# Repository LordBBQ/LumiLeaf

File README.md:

# LumiLeaf
Smart affordable adressable LED panels

### Assembly
##### Step 1

Remove the printed supports and adhesion materials from the part.

##### Step 2

Use a soldering iron to insert the 4 terminal heatset inserts.

Insert the M3 terminal bolts and washers into the inserts.

##### Step 3

Strip a length of solid core ethernet cable.

Separate the individual strands, and remove the twists as much as possible.

##### Step 4

Route the wires through the wire channel as shown.

##### Step 5

Cut a 250mm length of LED strip.

Adhere this around the edge of the light.

##### Step 6

Carefully solder the 4 wires to the 5V, GND, D+ and D- pins. This is very fiddly, and may require multiple attempts.

##### Step 7

Route the wires out the wire hole, and spread them to each of their terminals. 

Loop each wire around a bolt and tighten, ensuring there is no insulation clamped under the screw.

##### Step 8

Use a multimeter to check check for short circuts in the assembly.

##### Step 9

Cut out a triangular section of foil to act as the reflector.

Use a thin double sided tape to adhere the foil over the back panel.

>[!WARNING]
>Ensure the foil does not make contact with the LED strip or exposed wire. This could lead to a short circut!

##### Step 10
Repeat for all other desired modules. Attach the lasercut or 3D printed diffuser and bezel.

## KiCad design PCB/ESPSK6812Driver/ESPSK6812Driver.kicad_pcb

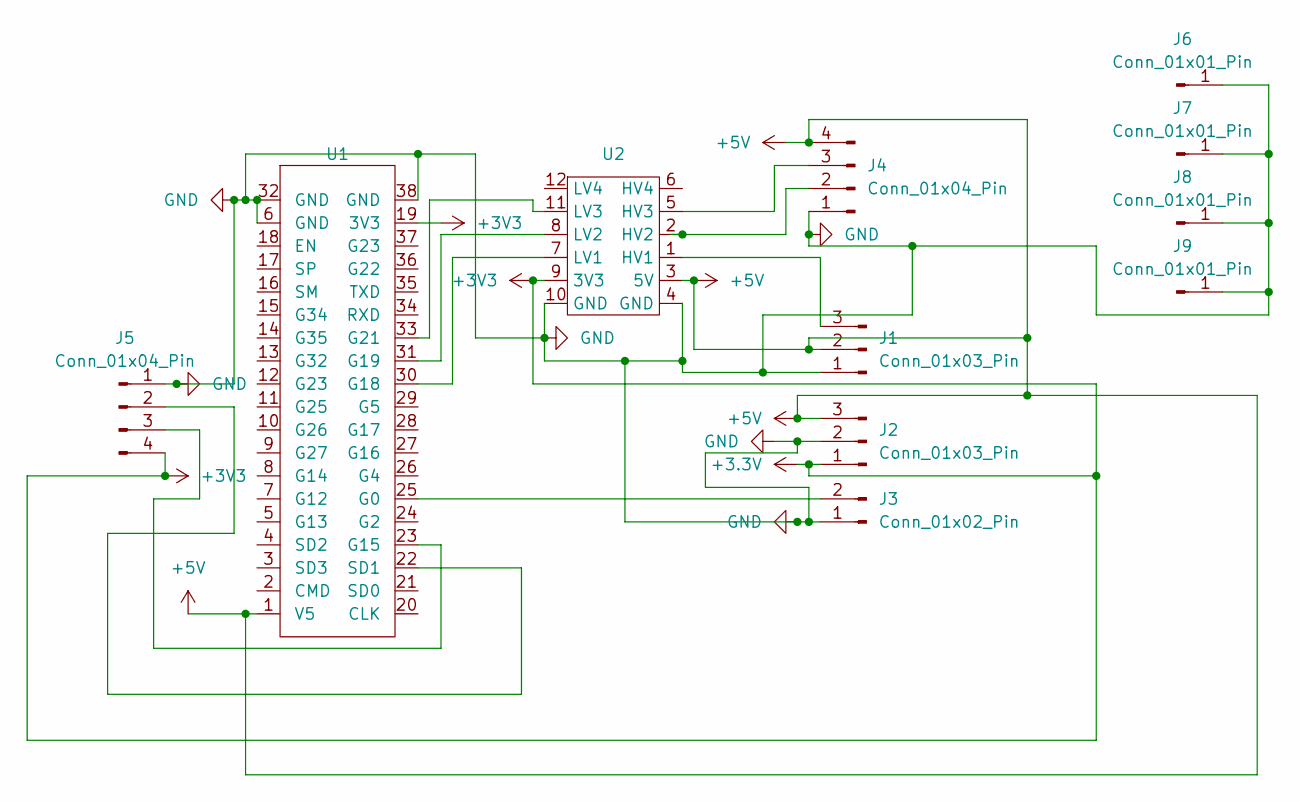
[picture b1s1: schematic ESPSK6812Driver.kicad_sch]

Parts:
J1, J2: Conn_01x03_Pin; JST_XH_B3B-XH-AM_1x03_P2.50mm_Vertical
J3: Conn_01x02_Pin; JST_XH_B2B-XH-AM_1x02_P2.50mm_Vertical
J4, J5: Conn_01x04_Pin; PinHeader_1x04_P2.54mm_Vertical
J6, J7, J8, J9: Conn_01x01_Pin; MountingHole_3.2mm_M3_DIN965_Pad
U1: ESPModuleJaycar
U2: LogicLevelShifterBidirectional

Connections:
+3.3V: J2.1, J5.4, U1.19 (3V3), U2.9 (3V3)
+5V: J1.2, J2.3, J4.4, U1.1 (V5), U2.3 (5V)
GND: J1.1, J2.2, J3.1, J4.1, J5.1, J6.1, J7.1, J8.1, J9.1, U1.6 (GND), U1.32 (GND), U1.38 (GND), U2.4 (GND), U2.10 (GND)
unnamed: J1.3, U2.1 (HV1)
unnamed: J3.2, U1.25 (G0)
unnamed: J4.2, U2.2 (HV2)
unnamed: J4.3, U2.5 (HV3)
unnamed: J5.2, U1.22 (SD1)
unnamed: J5.3, U1.23 (G15)
unnamed: U1.30 (G18), U2.7 (LV1)
unnamed: U1.31 (G19), U2.8 (LV2)
unnamed: U1.33 (G21), U2.11 (LV3)

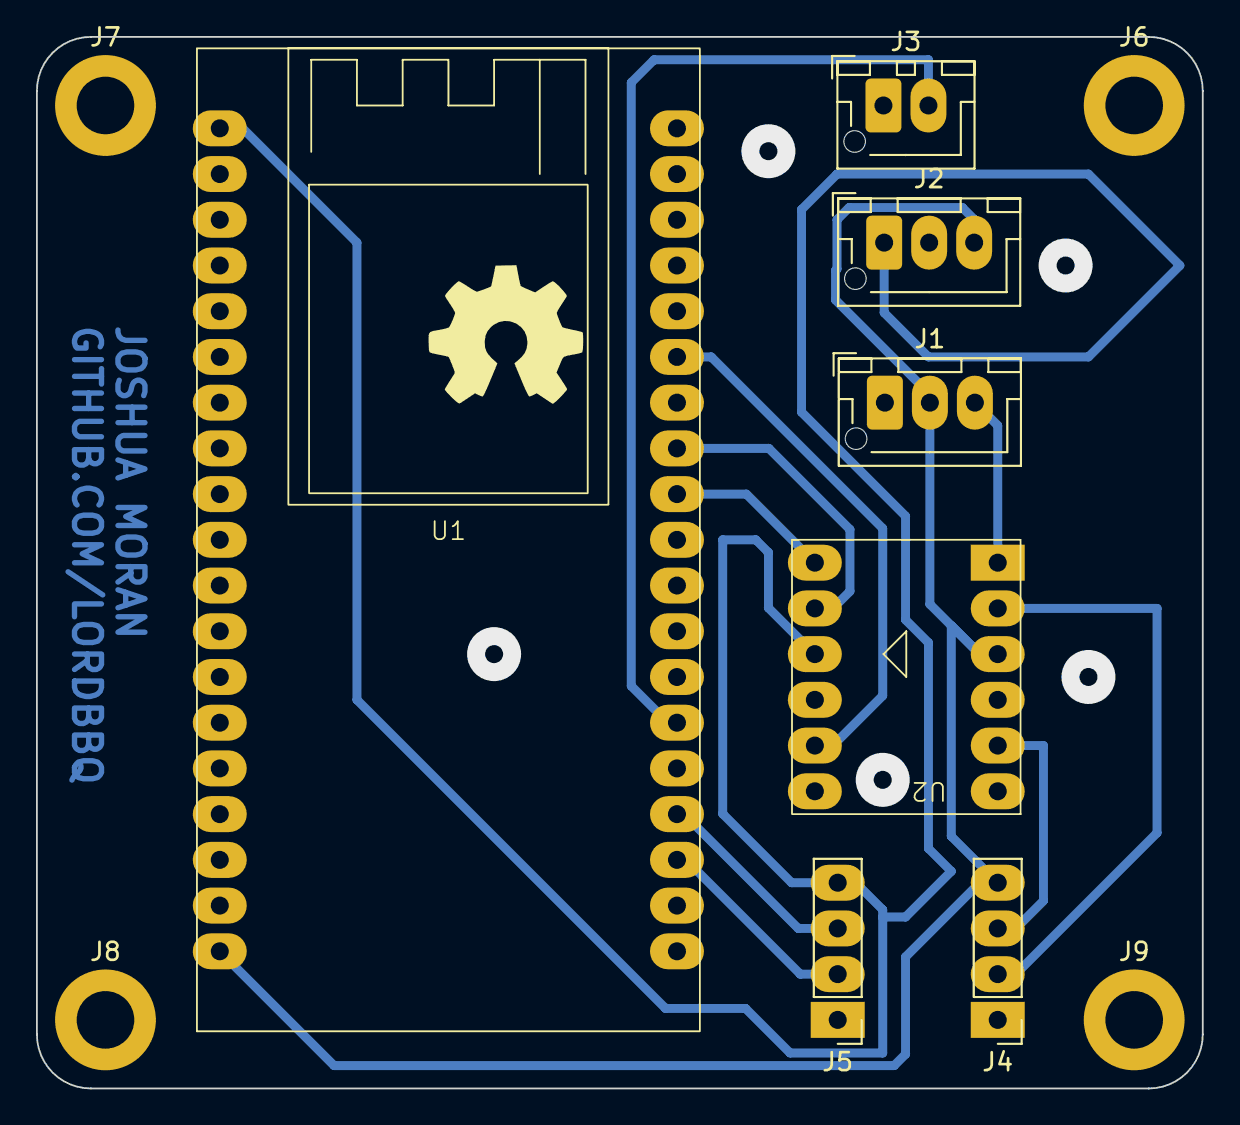
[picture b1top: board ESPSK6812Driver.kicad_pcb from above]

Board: 2 copper layers, 64.8 x 58.4 mm, 11 parts (0 on the bottom side), 12 nets.

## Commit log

2023-08-01 added base files
